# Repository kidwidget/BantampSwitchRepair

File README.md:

# BantampSwitchRepair
Kicad schematics and board to repair bantamp switch board

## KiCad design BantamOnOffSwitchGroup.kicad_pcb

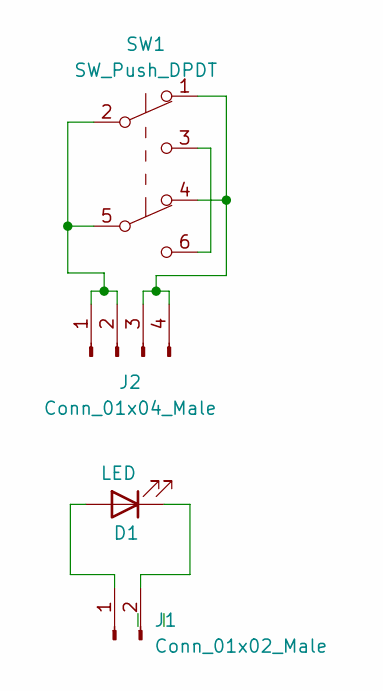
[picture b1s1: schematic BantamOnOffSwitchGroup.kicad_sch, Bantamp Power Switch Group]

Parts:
D1: LED; LED_D3.0mm
J1: Conn_01x02_Male; PinHeader_1x02_P2.54mm_Vertical
J2: Conn_01x04_Male; PinHeader_1x04_P2.54mm_Vertical
SW1: SW_Push_DPDT; Toggle_DPDT

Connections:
unnamed: D1.2 (A), J1.1
unnamed: D1.1 (K), J1.2
unnamed: J2.1, J2.2, SW1.2 (B), SW1.5 (B)
unnamed: J2.3, J2.4, SW1.1 (A), SW1.4 (A)
unnamed: SW1.3 (C), SW1.6 (C)

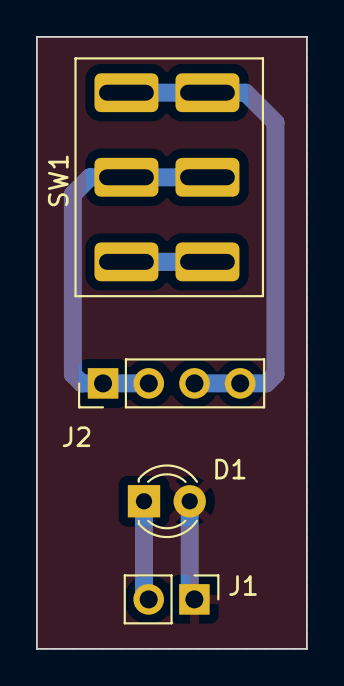
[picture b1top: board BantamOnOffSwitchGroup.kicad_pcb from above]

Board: 2 copper layers, 15.0 x 34.0 mm, 4 parts (0 on the bottom side), 5 nets.

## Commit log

2024-03-06 added copper pour, need to doublecheck measurements
2024-03-07 gbr and drill files created
2024-03-21 fixed spacing on switch legs
2024-03-21 fixed spacing on switch legs, twice
